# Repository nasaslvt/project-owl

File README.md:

# project-owl

## Repository Structure
- `beagle`: BeagleBone Black source code
- `conf`: Configuration files, especially for Dire Wolf
- `doc`: Documentation, including block diagrams and schematics
- `esp`: ESP32-CAM source code
- `kicad`: KiCad project files

## Documentation

Schematics were created with KiCad and follow the \<version>.\<subversion> naming convention.  
Block diagrams were created with DigiKey's online [SchemeIt tool](https://www.digikey.com/schemeit/project/project-owl-26cf1e4f4a01456586e33678977ee045).

## Configuration

#### Setup

Install rtl_test, rtl_fm, etc.
```bash
apt-get install rtl-sdr sox
```

Build and install the latest direwolf (1.6 at time of this writing)
```bash
sudo apt-get install git gcc g++ make cmake libasound2-dev libudev-dev
cd ~
mkdir src && cd src
git clone https://www.github.com/wb2osz/direwolf
mkdir build && cd build
cmake ..
make -j4
sudo make install
make install-conf
exit
```

Copy `receive.conf` from this repository to `~/conf/receive.conf`

### ESP32-Camera

#### Flashing

todo

## Operation
### Using rtl_fm
[Reference guide](http://kmkeen.com/rtl-demod-guide/).
To listen to FM radio: `rtl_fm -M wbfm -f 90.7M | sox -r 32k -t raw -e s -b 16 -c 1 -V1 - test.wav`
To use rtl_fm and Dire Wolf: `rtl_fm  -f 145.70M - | direwolf -c receive.conf` or run `receive.sh`.
We are using **145.70 MHz** as our test frequency, although APRS for North America is 144.39M. 

## Debugging
The user running Dire Wolf must be a member of the `audio` group.

## Licensing
The KiCad footprint and model for the L101011MS02Q were provided by SnapEDA under the CC-BY-SA 4.0 license: https://www.snapeda.com/parts/L101011MS02Q/C&K/view-part/?ref=digikey

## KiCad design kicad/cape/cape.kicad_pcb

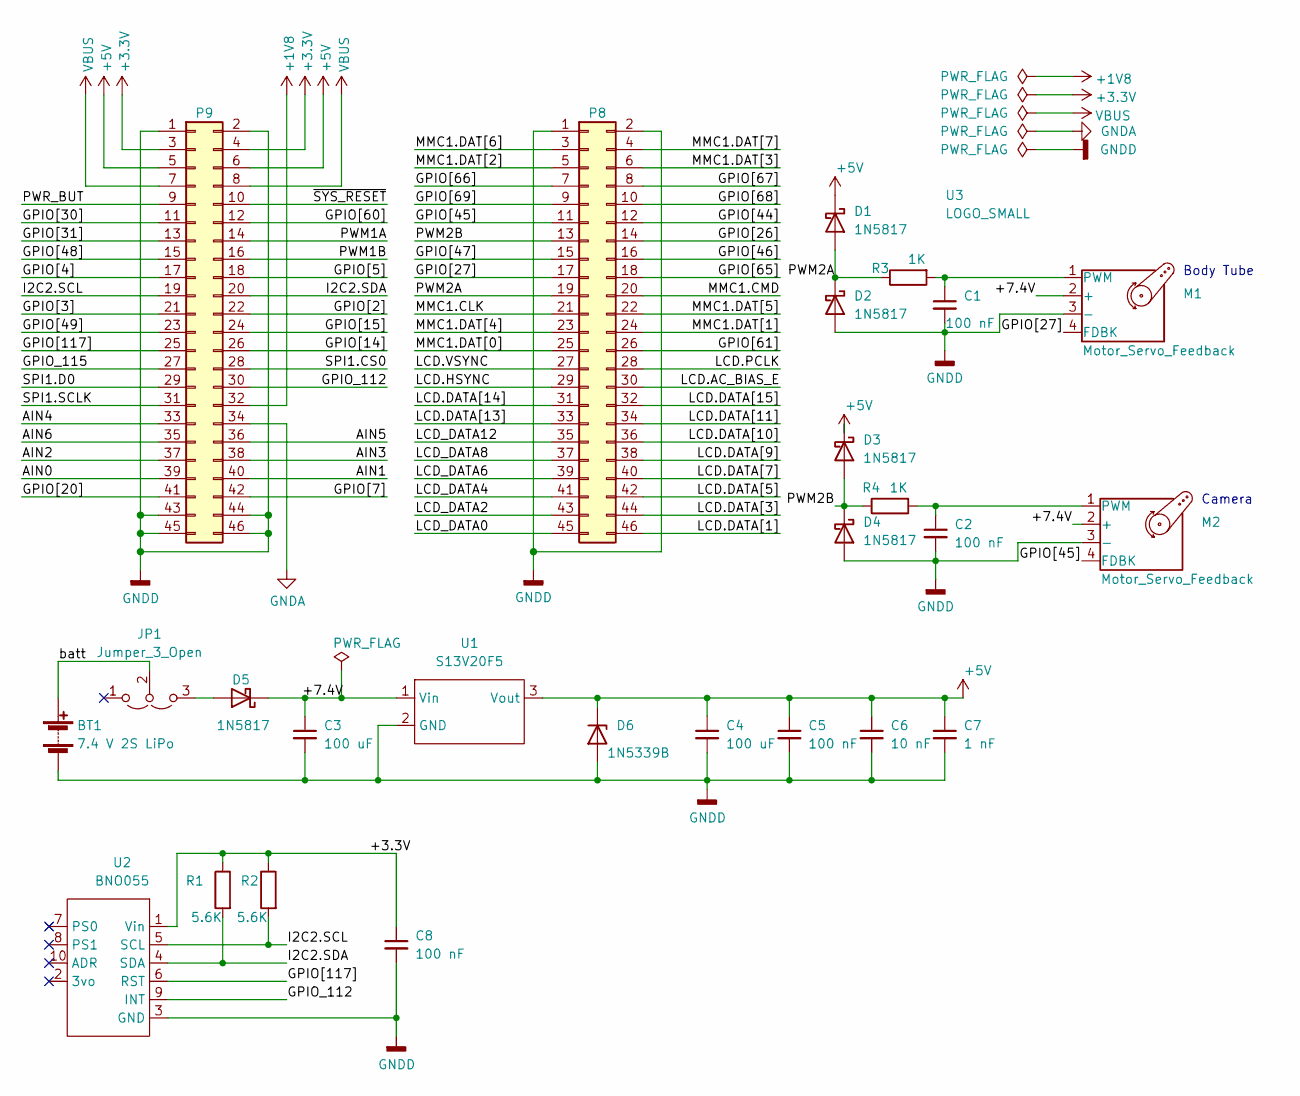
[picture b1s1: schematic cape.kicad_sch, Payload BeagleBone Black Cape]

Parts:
BT1: 7.4 V 2S LiPo; PinHeader_2x01_P2.54mm_Vertical
C1, C2, C5, C8: 100 nF; C_Disc_D4.7mm_W2.5mm_P5.00mm
C3: 100 uF; C_Radial_D8.0mm_H11.5mm_P3.50mm
C4: 100 uF; C_Radial_D8.0mm_H7.0mm_P3.50mm
C6: 10 nF; C_Disc_D4.7mm_W2.5mm_P5.00mm
C7: 1 nF; C_Disc_D4.7mm_W2.5mm_P5.00mm
D1, D2, D3, D4, D5: 1N5817; D_DO-41_SOD81_P10.16mm_Horizontal
D6: 1N5339B; D_DO-201_P15.24mm_Horizontal
JP1: Jumper_3_Open; PinHeader_1x03_P2.54mm_Vertical
M1, M2: Motor_Servo_Feedback; FeedbackServo
P8, P9: BeagleBone_Black_Header; PinHeader_2x23_P2.54mm_Vertical
R1, R2: 5.6K; R_Axial_DIN0207_L6.3mm_D2.5mm_P15.24mm_Horizontal
R3, R4: 1K; R_Axial_DIN0207_L6.3mm_D2.5mm_P15.24mm_Horizontal
U1: S13V20F5; S13V10F5
U2: BNO055
U3: LOGO_SMALL; logo

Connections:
+1V8: P9.32
+3.3V: C8.1, P9.3, P9.4, R1.1, R2.1, U2.1 (Vin)
+5V: C4.1, C5.1, C6.1, C7.1, D1.1 (K), D3.1 (K), D6.1 (K), P9.5, P9.6, U1.3 (Vout)
/+7.4V: C3.1, D5.1 (K), M1.2 (+), M2.2 (+), U1.1 (Vin)
/AIN0: P9.39
/AIN1: P9.40
/AIN2: P9.37
/AIN3: P9.38
/AIN4: P9.33
/AIN5: P9.36
/AIN6: P9.35
/GPIO[2]: P9.22
/GPIO[3]: P9.21
/GPIO[4]: P9.17
/GPIO[5]: P9.18
/GPIO[7]: P9.42
/GPIO[14]: P9.26
/GPIO[15]: P9.24
/GPIO[20]: P9.41
/GPIO[26]: P8.14
/GPIO[27]: M1.4 (FDBK), P8.17
/GPIO[30]: P9.11
/GPIO[31]: P9.13
/GPIO[44]: P8.12
/GPIO[45]: M2.4 (FDBK), P8.11
/GPIO[46]: P8.16
/GPIO[47]: P8.15
/GPIO[48]: P9.15
/GPIO[49]: P9.23
/GPIO[60]: P9.12
/GPIO[61]: P8.26
/GPIO[65]: P8.18
/GPIO[66]: P8.7
/GPIO[67]: P8.8
/GPIO[68]: P8.10
/GPIO[69]: P8.9
/GPIO[117]: P9.25, U2.6 (RST)
/GPIO_112: P9.30, U2.9 (INT)
/GPIO_115: P9.27
/I2C2.SCL: P9.19, R2.2, U2.5 (SCL)
/I2C2.SDA: P9.20, R1.2, U2.4 (SDA)
/LCD.AC_BIAS_E: P8.30
/LCD.DATA[1]: P8.46
/LCD.DATA[3]: P8.44
/LCD.DATA[5]: P8.42
/LCD.DATA[7]: P8.40
/LCD.DATA[9]: P8.38
/LCD.DATA[10]: P8.36
/LCD.DATA[11]: P8.34
/LCD.DATA[13]: P8.33
/LCD.DATA[14]: P8.31
/LCD.DATA[15]: P8.32
/LCD.HSYNC: P8.29
/LCD.PCLK: P8.28
/LCD.VSYNC: P8.27
/LCD_DATA0: P8.45
/LCD_DATA2: P8.43
/LCD_DATA4: P8.41
/LCD_DATA6: P8.39
/LCD_DATA8: P8.37
/LCD_DATA12: P8.35
/MMC1.CLK: P8.21
/MMC1.CMD: P8.20
/MMC1.DAT[0]: P8.25
/MMC1.DAT[1]: P8.24
/MMC1.DAT[2]: P8.5
/MMC1.DAT[3]: P8.6
/MMC1.DAT[4]: P8.23
/MMC1.DAT[5]: P8.22
/MMC1.DAT[6]: P8.3
/MMC1.DAT[7]: P8.4
/PWM1A: P9.14
/PWM1B: P9.16
/PWM2A: D1.2 (A), D2.1 (K), P8.19, R3.1
/PWM2B: D3.2 (A), D4.1 (K), P8.13, R4.1
/PWR_BUT: P9.9
/SPI1.CS0: P9.28
/SPI1.D0: P9.29
/SPI1.SCLK: P9.31
/batt: BT1.1 (+), JP1.2 (C)
/~SYS_RESET: P9.10
GNDA: P9.34
GNDD: BT1.2 (-), C1.2, C2.2, C3.2, C4.2, C5.2, C6.2, C7.2, C8.2, D2.2 (A), D4.2 (A), D6.2 (A), M1.3 (-), M2.3 (-), P8.1, P8.2, P9.1, P9.2, P9.43, P9.44, P9.45, P9.46, U1.2 (GND), U2.3 (GND)
unnamed: C1.1, M1.1 (PWM), R3.2
unnamed: C2.1, M2.1 (PWM), R4.2
unnamed: D5.2 (A), JP1.3 (B)
VBUS: P9.7, P9.8

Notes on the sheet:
Camera
Body Tube

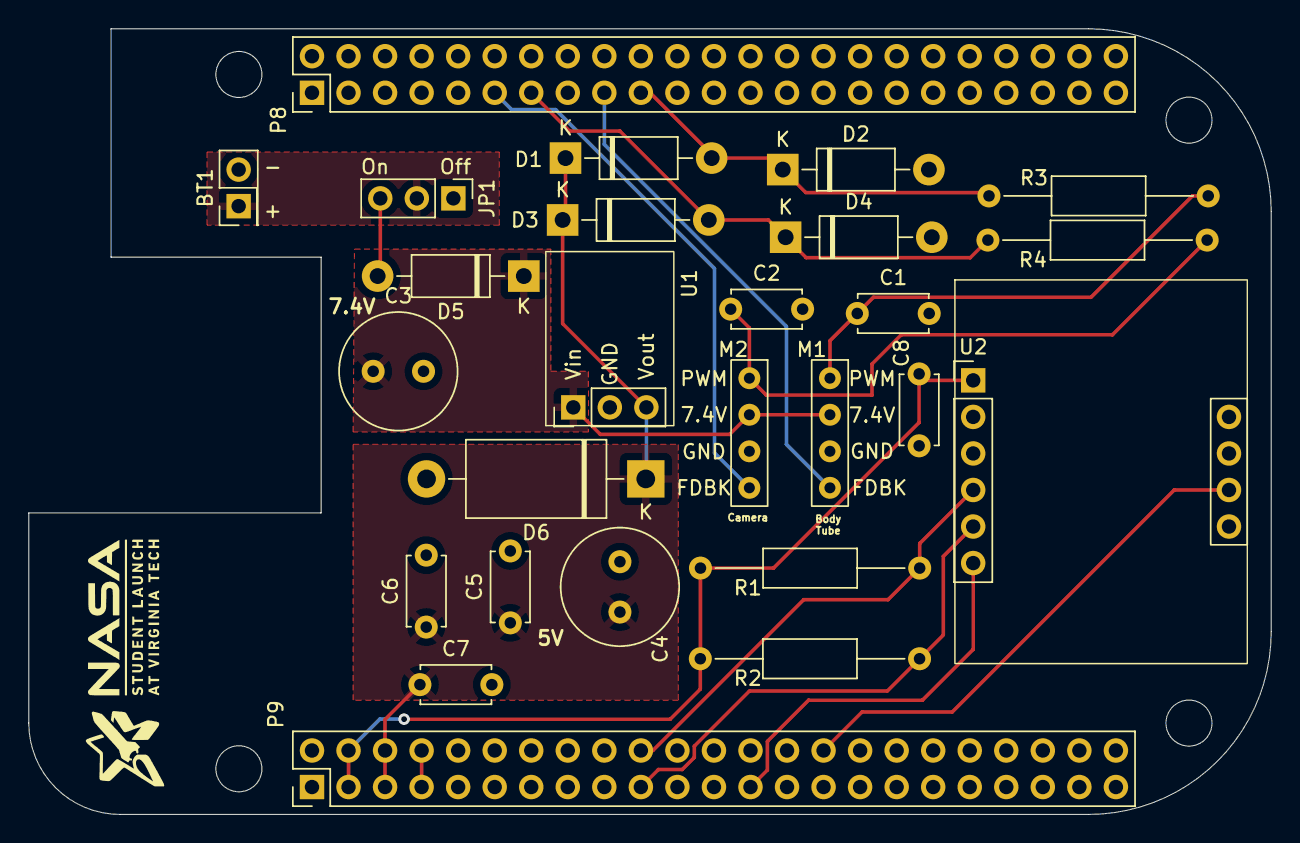
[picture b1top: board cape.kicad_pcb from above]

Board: 2 copper layers, 86.4 x 54.6 mm, 31 parts (0 on the bottom side), 17 nets.

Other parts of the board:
MH1, MH2, MH3, MH4: MountingHole_3.2mm_M3_DIN965

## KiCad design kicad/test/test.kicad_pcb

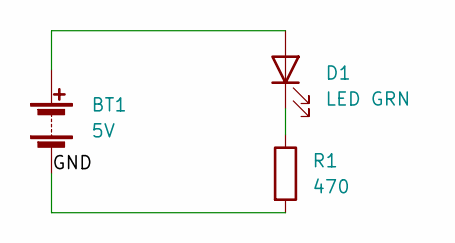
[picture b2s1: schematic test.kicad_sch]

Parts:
BT1: 5V; PinHeader_2x01_P2.54mm_Vertical
D1: LED GRN; LED_D5.0mm
R1: 470; R_Axial_DIN0309_L9.0mm_D3.2mm_P15.24mm_Horizontal

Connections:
/GND: BT1.2 (-), R1.2
unnamed: BT1.1 (+), D1.2 (A)
unnamed: D1.1 (K), R1.1

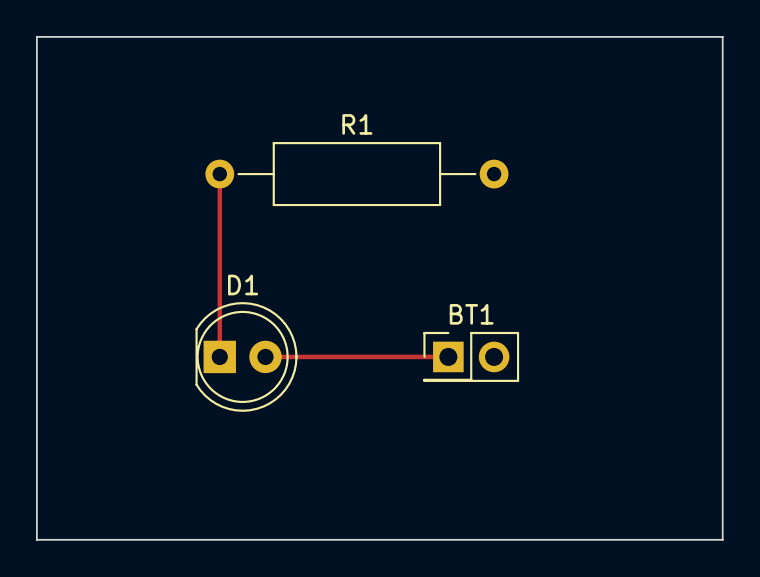
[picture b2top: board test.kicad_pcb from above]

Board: 2 copper layers, 38.1 x 27.9 mm, 3 parts (0 on the bottom side), 3 nets.

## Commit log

2022-10-23 Began writing BeagleBone Black configuration documentation. Added direwolf.conf
2022-10-23 renamed direwolf.conf to transmit.conf, minor readme updates
2022-10-23 added receive.conf
2022-10-30 Receive and transmit config files cleaned to minimum required. Script created for receiving
2022-10-30 created client.cpp; incomplete
2022-10-30 working client connection code: sends integer test
2022-10-30 Client code works but struct sockaddr_in pointer is broken
2022-11-04 Removed struct pointer, using regular struct. Working well.
2022-11-05 Separated into tcp.h and tcp.cpp. Added kiss transmit and receive programs. Tested, working.
2022-11-05 minor comment fix
2022-11-05 added file header comments
2022-11-05 Restructured directory, added makefile
2022-11-05 added build to .gitignore
2022-11-05 Created kiss_parser; end-to-end transmission (NASA message to command enum) works.
2022-11-11 Separated parsing into parser.h/cpp, improved makefile to use variables.
2022-11-13 Renamed files. Need to update makefile.
2022-12-16 Created main_v1 schematic.
2022-12-16 Created revision 1.1 of main_v1
2022-12-16 main_v1.2 schematic
2022-12-16 Created v1-3, added kill switch
2022-12-16 Camera schematic v1
2022-12-17 Changed library path, main_v1-4 and cam_v1-1 and Project-OWL block diagrams
2022-12-17 Updated gitignore, readme
2022-12-18 Started cape
2022-12-18 first working revision of cape done
2022-12-19 Finished second revision of cape, basically print-ready
2022-12-19 Moved cape pdf files to doc
2022-12-29 Preparing to update schematics
2022-12-29 Exported block diagram
2022-12-29 Updated main to 1.5
2022-12-29 Main 1.6, Cam 1.2, added pwr flags and not connected markers to eliminate ERC violations
2022-12-30 Cape v 1.2
2022-12-30 Cape 1.3, Main 1.7
2022-12-30 Genereated step model and moved old doc to Old folder
2022-12-30 Updated all schematics
2023-01-03 Enalrged bno055 footprint pins, made final gerbers
2023-01-03 Exported gerber to JLC PCB
2023-01-03 Additional clean commit
2023-01-05 Updated block diagram to S13V20F5
2023-01-29 Networking
2023-02-03 Stream
2023-02-05 Working on post-build payload changes
2023-02-10 Cape v1-5
2023-02-11 New endpoints
2023-02-25 failure analysis images
2023-02-25 Finished schematic v1-5
2023-02-25 Finished cape v1-5
2023-03-14 c lib
2023-03-14 main loop
2023-03-17 control
2023-03-19 servo
2023-03-19 bno support
2023-03-25 rotation and swivel fixed
